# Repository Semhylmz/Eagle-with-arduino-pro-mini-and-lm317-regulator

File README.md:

# Autodesk Eagle-with-lm317-regulator

PCB design consisting of Arduino pro mini, lm317 regulator integrated, two relay and optocoupler circuits.

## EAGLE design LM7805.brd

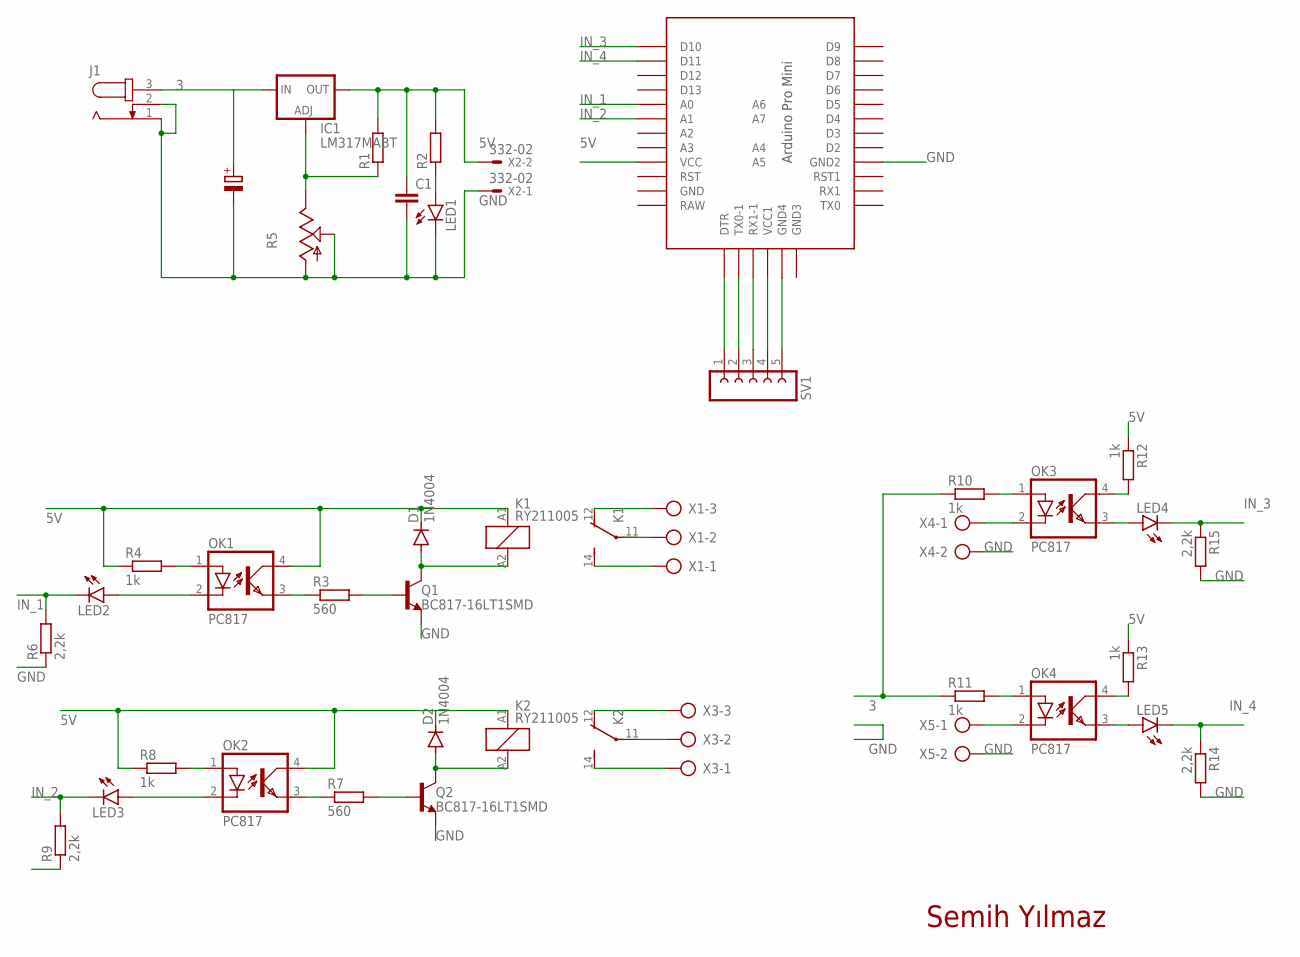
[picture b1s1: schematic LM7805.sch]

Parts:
C1: C2.5/2; C2.5-2
D1, D2: 1N4004; DO41-10
IC1: LM317MABT; TO220L1
J1: JACK-PLUG1; SPC4078
K1, K2: RY211005; RY-II
LED1, LED2, LED3, LED4, LED5: LED3MM
OK1, OK2, OK3, OK4: PC817; DIL04
Q1, Q2: BC817-16LT1SMD; SOT23-BEC
R1, R2: R-EU_0204/7; 0204/7
R3, R7: 560; 0204/7
R4, R8, R10, R11, R12, R13: 1k; 0204/7
R5: TRIM_US-S64W; S64W
R6, R9, R14, R15: 2,2k; 0204/7
SV1: FE05-1
U$1: PRO-MINI-2
X1, X3: AK300/3
X2: 332-02
X4, X5: AK300/2

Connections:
3: IC1.3 (IN), J1.3, R10.1, R11.1
5V: C1.1, D1.C, D2.C, IC1.2 (OUT), K1.A1 (1), K2.A1 (1), OK1.4 (COL), OK2.4 (COL), R1.2, R2.2, R4.1, R8.1, R12.1, R13.1, U$1.VCC, X2.2
GND: C1.2, J1.1, J1.2, LED1.K (C), Q1.E, Q2.E, R5.A, R5.S, R6.1, R9.1, R14.2, R15.2, U$1.GND1 (GND2), X2.1, X4.2, X5.2
IN_1: LED2.K (C), R6.2, U$1.A0
IN_2: LED3.K (C), R9.2, U$1.A1
IN_3: LED4.K (C), R15.1, U$1.D10
IN_4: LED5.K (C), R14.1, U$1.D11
unnamed: SV1.1, U$1.DTR
unnamed: SV1.2, U$1.TX0-1
unnamed: K1.11, X1.2
unnamed: SV1.3, U$1.RX1-1
unnamed: LED1.A, R2.1
unnamed: IC1.1 (ADJ), R1.1, R5.E
unnamed: SV1.4, U$1.VCC1
unnamed: SV1.5, U$1.GND3 (GND4)
unnamed: OK1.1 (A), R4.2
unnamed: K1.12 (O), X1.3
unnamed: LED2.A, OK1.2 (C)
unnamed: OK1.3 (EMIT), R3.1
unnamed: K1.14 (S), X1.1
unnamed: D1.A, K1.A2 (2), Q1.C
unnamed: LED3.A, OK2.2 (C)
unnamed: Q2.B, R7.2
unnamed: OK2.1 (A), R8.2
unnamed: OK2.3 (EMIT), R7.1
unnamed: Q1.B, R3.2
unnamed: D2.A, K2.A2 (2), Q2.C
unnamed: K2.11, X3.2
unnamed: K2.12 (O), X3.3
unnamed: K2.14 (S), X3.1
unnamed: OK3.4 (COL), R12.2
unnamed: LED4.A, OK3.3 (EMIT)
unnamed: OK4.4 (COL), R13.2
unnamed: LED5.A, OK4.3 (EMIT)
unnamed: OK4.2 (C), X5.1
unnamed: OK4.1 (A), R11.2
unnamed: OK3.2 (C), X4.1
unnamed: OK3.1 (A), R10.2

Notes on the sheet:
Semih Yılmaz

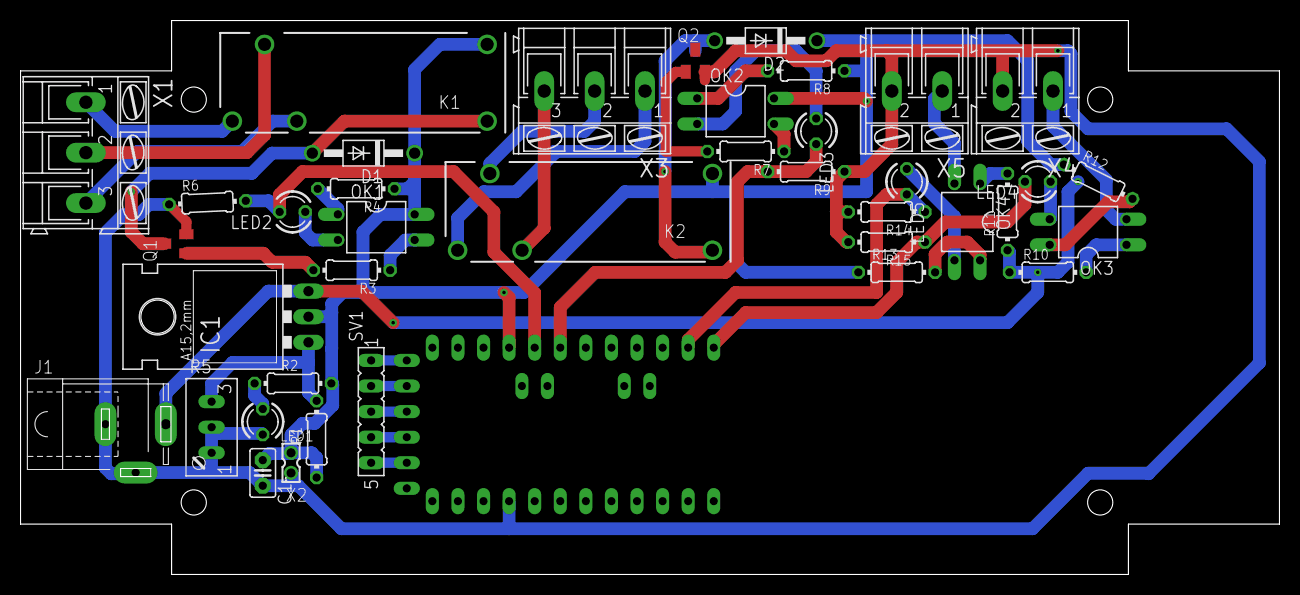
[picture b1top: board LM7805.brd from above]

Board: 2 copper layers, 125.0 x 55.0 mm, 40 parts (0 on the bottom side), 38 nets.
